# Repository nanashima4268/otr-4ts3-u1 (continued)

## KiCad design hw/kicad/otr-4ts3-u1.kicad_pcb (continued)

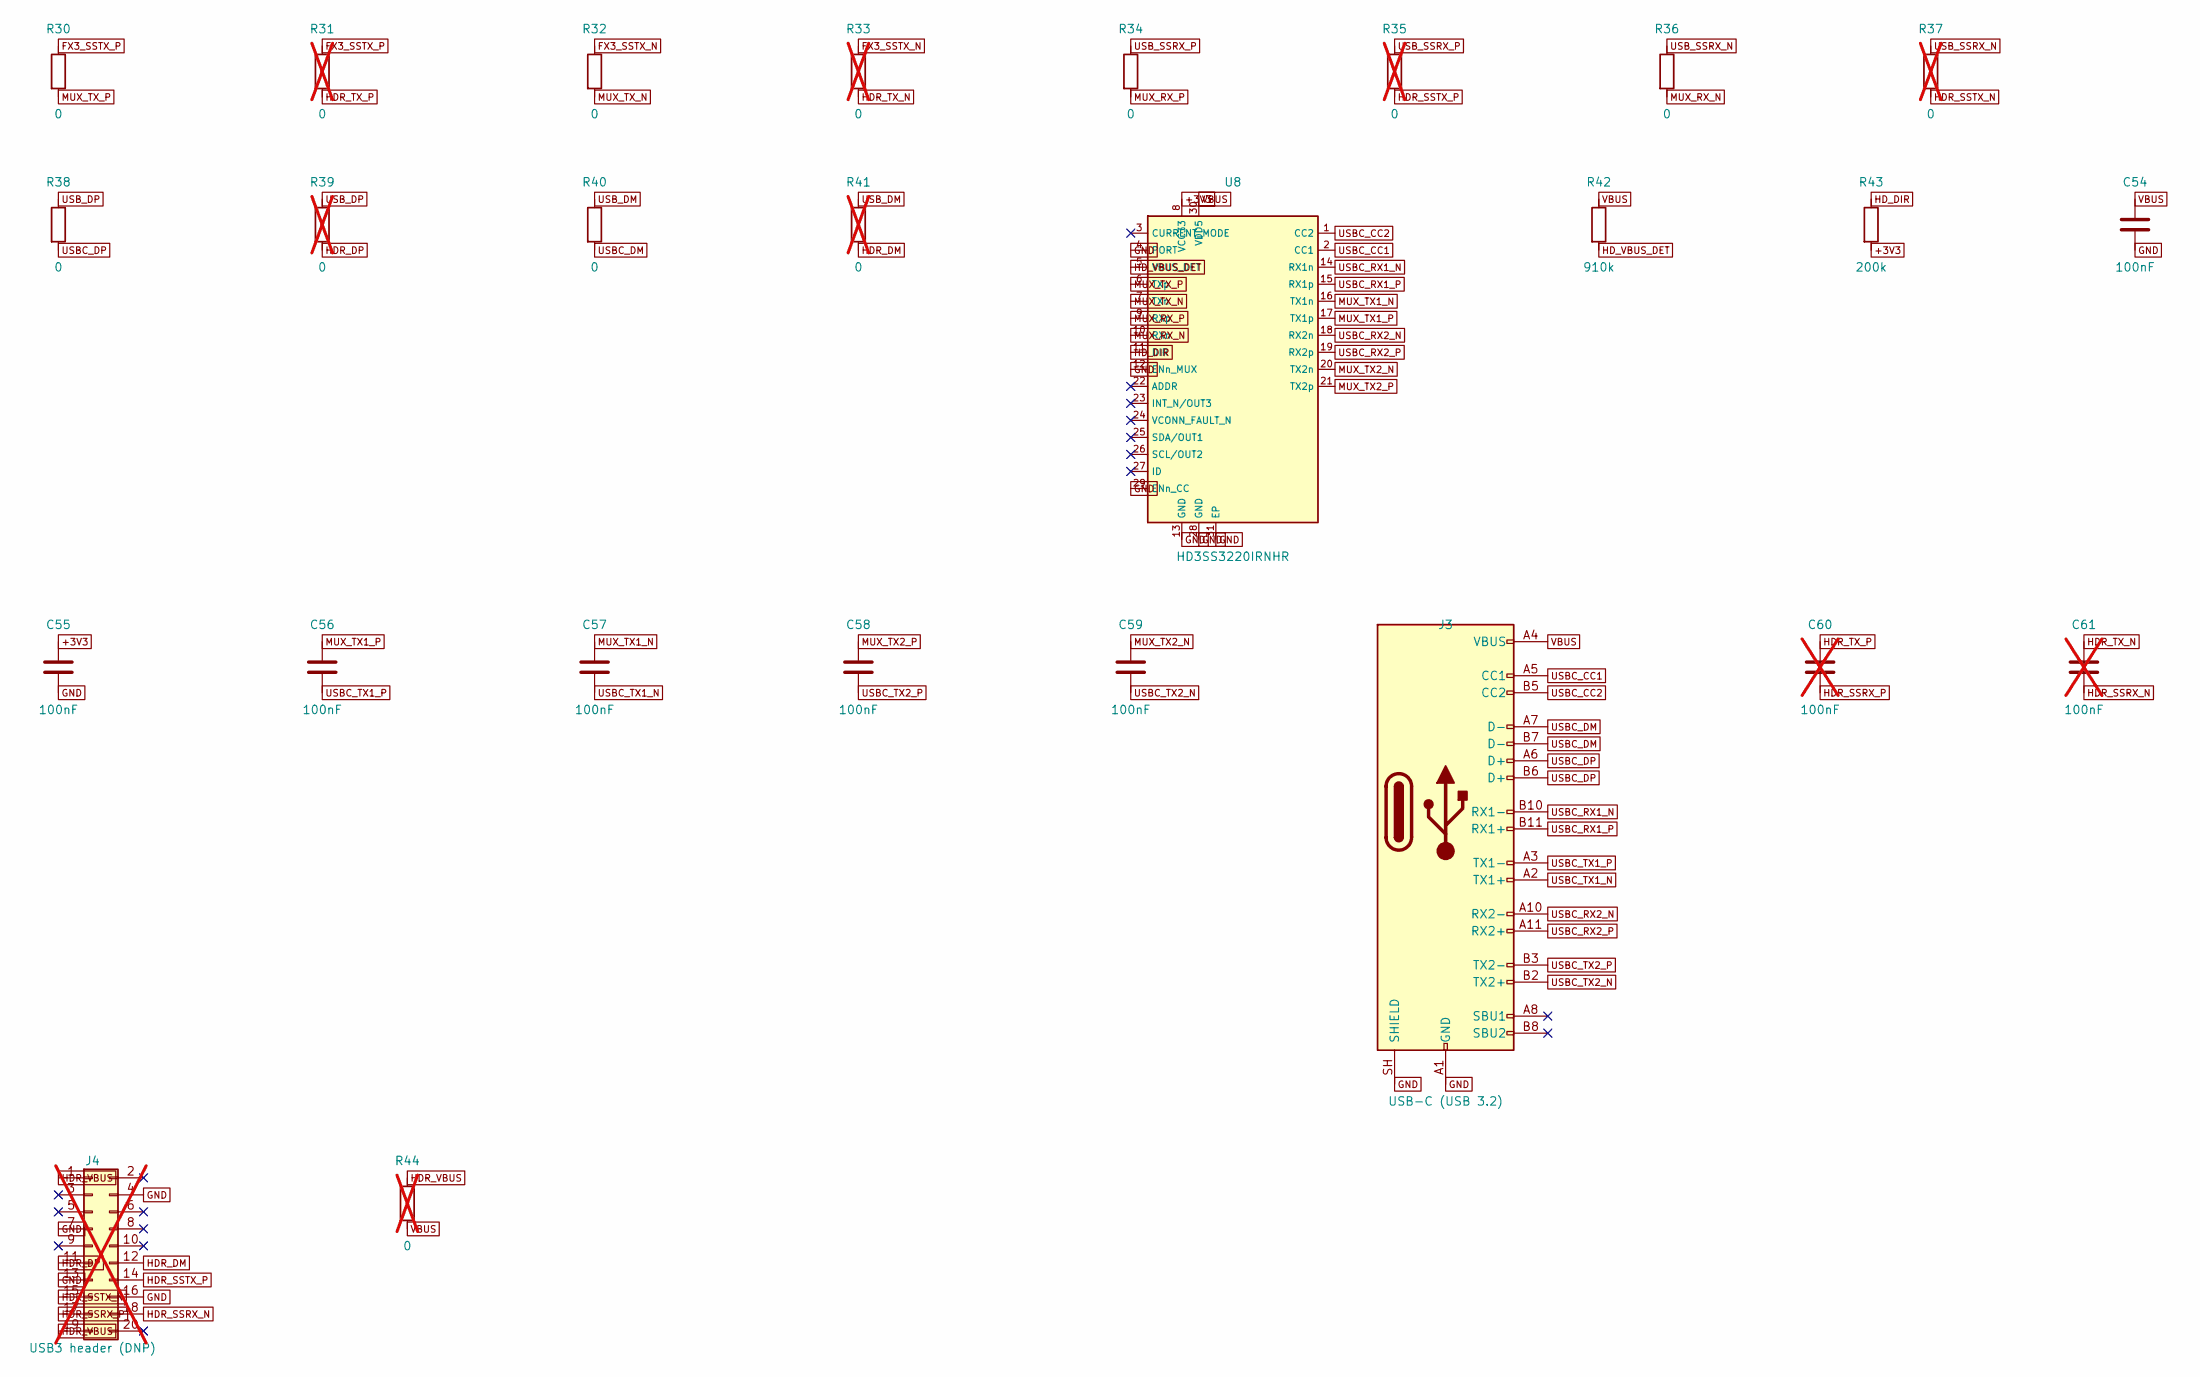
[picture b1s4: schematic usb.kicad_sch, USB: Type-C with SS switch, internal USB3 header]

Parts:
C54, C55, C56, C57, C58, C59: 100nF; C_0402_1005Metric; LCSC C1525
C60, C61: 100nF; C_0402_1005Metric; LCSC C1525; not fitted
J3: USB-C (USB 3.2); USB_C_Receptacle_SameSky_UJ32-C-H-G-H2-SMT; LCSC C22359755
J4: USB3 header (DNP); PinHeader_2x10_P2.00mm_Vertical; not fitted
R30, R32, R34, R36, R38, R40: 0; R_0402_1005Metric; LCSC C17168
R31, R33, R35, R37, R39, R41, R44: 0; R_0402_1005Metric; LCSC C17168; not fitted
R42: 910k; R_0402_1005Metric; LCSC C2909391
R43: 200k; R_0402_1005Metric; LCSC C25764
U8: HD3SS3220IRNHR; Texas_RNH0030A_WQFN-30-1EP_2.5x4.5mm_P0.4mm_EP1.2x3.2mm; LCSC C701817

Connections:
+3V3: C55.1, R43.2, U8.8 (VCC33); also elsewhere on the board
FX3_SSTX_N: R32.1, R33.1; also elsewhere on the board
FX3_SSTX_P: R30.1, R31.1; also elsewhere on the board
GND: C54.2, C55.2, J3.A1 (GND), J3.A12 (GND), J3.B1 (GND), J3.B12 (GND), J3.SH (SHIELD), J4.4, J4.7, J4.13, J4.16, U8.4 (PORT), U8.12 (ENn_MUX), U8.13 (GND), U8.28 (GND), U8.29 (ENn_CC), U8.31 (EP); also elsewhere on the board
HDR_DM: J4.12, R41.2
HDR_DP: J4.11, R39.2
HDR_SSRX_N: C61.2, J4.18
HDR_SSRX_P: C60.2, J4.17
HDR_SSTX_N: J4.15, R37.2
HDR_SSTX_P: J4.14, R35.2
HDR_TX_N: C61.1, R33.2
HDR_TX_P: C60.1, R31.2
HDR_VBUS: J4.1, J4.19, R44.1
HD_DIR: R43.1, U8.11 (DIR)
HD_VBUS_DET: R42.2, U8.5 (VBUS_DET)
MUX_RX_N: R36.2, U8.10 (RXn)
MUX_RX_P: R34.2, U8.9 (RXp)
MUX_TX1_N: C57.1, U8.16 (TX1n)
MUX_TX1_P: C56.1, U8.17 (TX1p)
MUX_TX2_N: C59.1, U8.20 (TX2n)
MUX_TX2_P: C58.1, U8.21 (TX2p)
MUX_TX_N: R32.2, U8.7 (TXn)
MUX_TX_P: R30.2, U8.6 (TXp)
USBC_CC1: J3.A5 (CC1), U8.2 (CC1)
USBC_CC2: J3.B5 (CC2), U8.1 (CC2)
USBC_DM: J3.A7 (D-), J3.B7 (D-), R40.2
USBC_DP: J3.A6 (D+), J3.B6 (D+), R38.2
USBC_RX1_N: J3.B10 (RX1-), U8.14 (RX1n)
USBC_RX1_P: J3.B11 (RX1+), U8.15 (RX1p)
USBC_RX2_N: J3.A10 (RX2-), U8.18 (RX2n)
USBC_RX2_P: J3.A11 (RX2+), U8.19 (RX2p)
USBC_TX1_N: C57.2, J3.A2 (TX1+)
USBC_TX1_P: C56.2, J3.A3 (TX1-)
USBC_TX2_N: C59.2, J3.B2 (TX2+)
USBC_TX2_P: C58.2, J3.B3 (TX2-)
USB_DM: R40.1, R41.1; also elsewhere on the board
USB_DP: R38.1, R39.1; also elsewhere on the board
USB_SSRX_N: R36.1, R37.1; also elsewhere on the board
USB_SSRX_P: R34.1, R35.1; also elsewhere on the board
VBUS: C54.1, J3.A4 (VBUS), J3.A9 (VBUS), J3.B4 (VBUS), J3.B9 (VBUS), R42.1, R44.2, U8.30 (VDD5); also elsewhere on the board

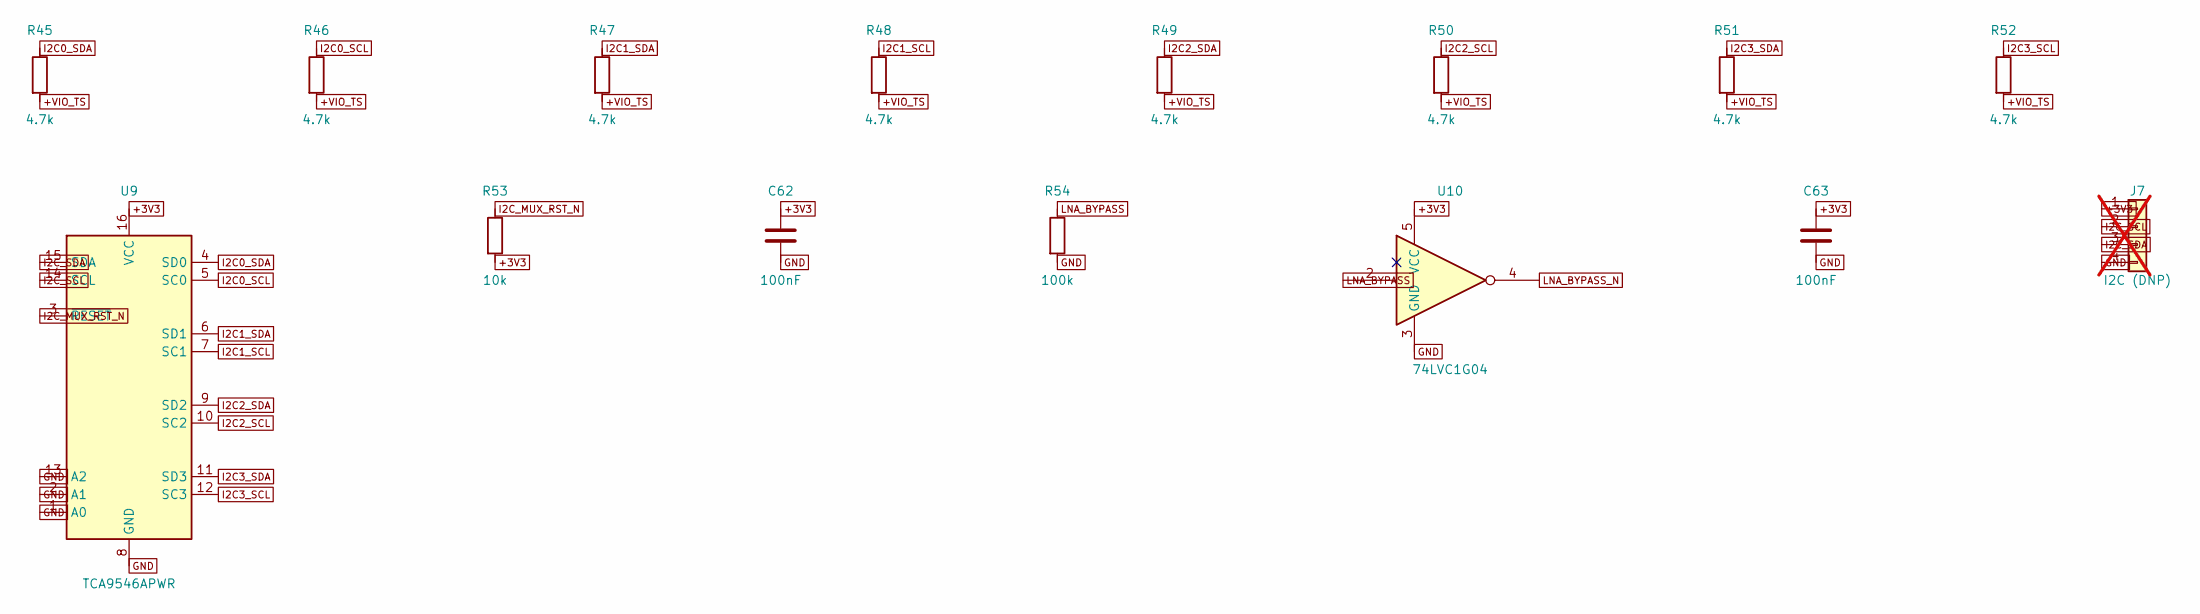
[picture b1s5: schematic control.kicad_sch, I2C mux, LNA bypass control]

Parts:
C62, C63: 100nF; C_0402_1005Metric; LCSC C1525
J7: I2C (DNP); PinHeader_1x04_P2.54mm_Vertical; not fitted
R45, R46, R47, R48, R49, R50, R51, R52: 4.7k; R_0402_1005Metric; LCSC C25900
R53: 10k; R_0402_1005Metric; LCSC C25744
R54: 100k; R_0402_1005Metric; LCSC C25741
U9: TCA9546APWR; TSSOP-16_4.4x5mm_P0.65mm; LCSC C201653
U10: 74LVC1G04; SOT-353_SC-70-5; LCSC C264081

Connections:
+3V3: C62.1, C63.1, J7.1, R53.2, U9.16 (VCC), U10.5 (VCC); also elsewhere on the board
+VIO_TS: R45.2, R46.2, R47.2, R48.2, R49.2, R50.2, R51.2, R52.2; also elsewhere on the board
GND: C62.2, C63.2, J7.4, R54.2, U9.1 (A0), U9.2 (A1), U9.8 (GND), U9.13 (A2), U10.3 (GND); also elsewhere on the board
I2C0_SCL: R46.1, U9.5 (SC0)
I2C0_SDA: R45.1, U9.4 (SD0)
I2C1_SCL: R48.1, U9.7 (SC1)
I2C1_SDA: R47.1, U9.6 (SD1)
I2C2_SCL: R50.1, U9.10 (SC2)
I2C2_SDA: R49.1, U9.9 (SD2)
I2C3_SCL: R52.1, U9.12 (SC3)
I2C3_SDA: R51.1, U9.11 (SD3)
I2C_MUX_RST_N: R53.1, U9.3 (~RESET)
I2C_SCL: J7.2, U9.14 (SCL); also elsewhere on the board
I2C_SDA: J7.3, U9.15 (SDA); also elsewhere on the board
LNA_BYPASS: R54.1, U10.2; also elsewhere on the board
LNA_BYPASS_N: U10.4; also elsewhere on the board

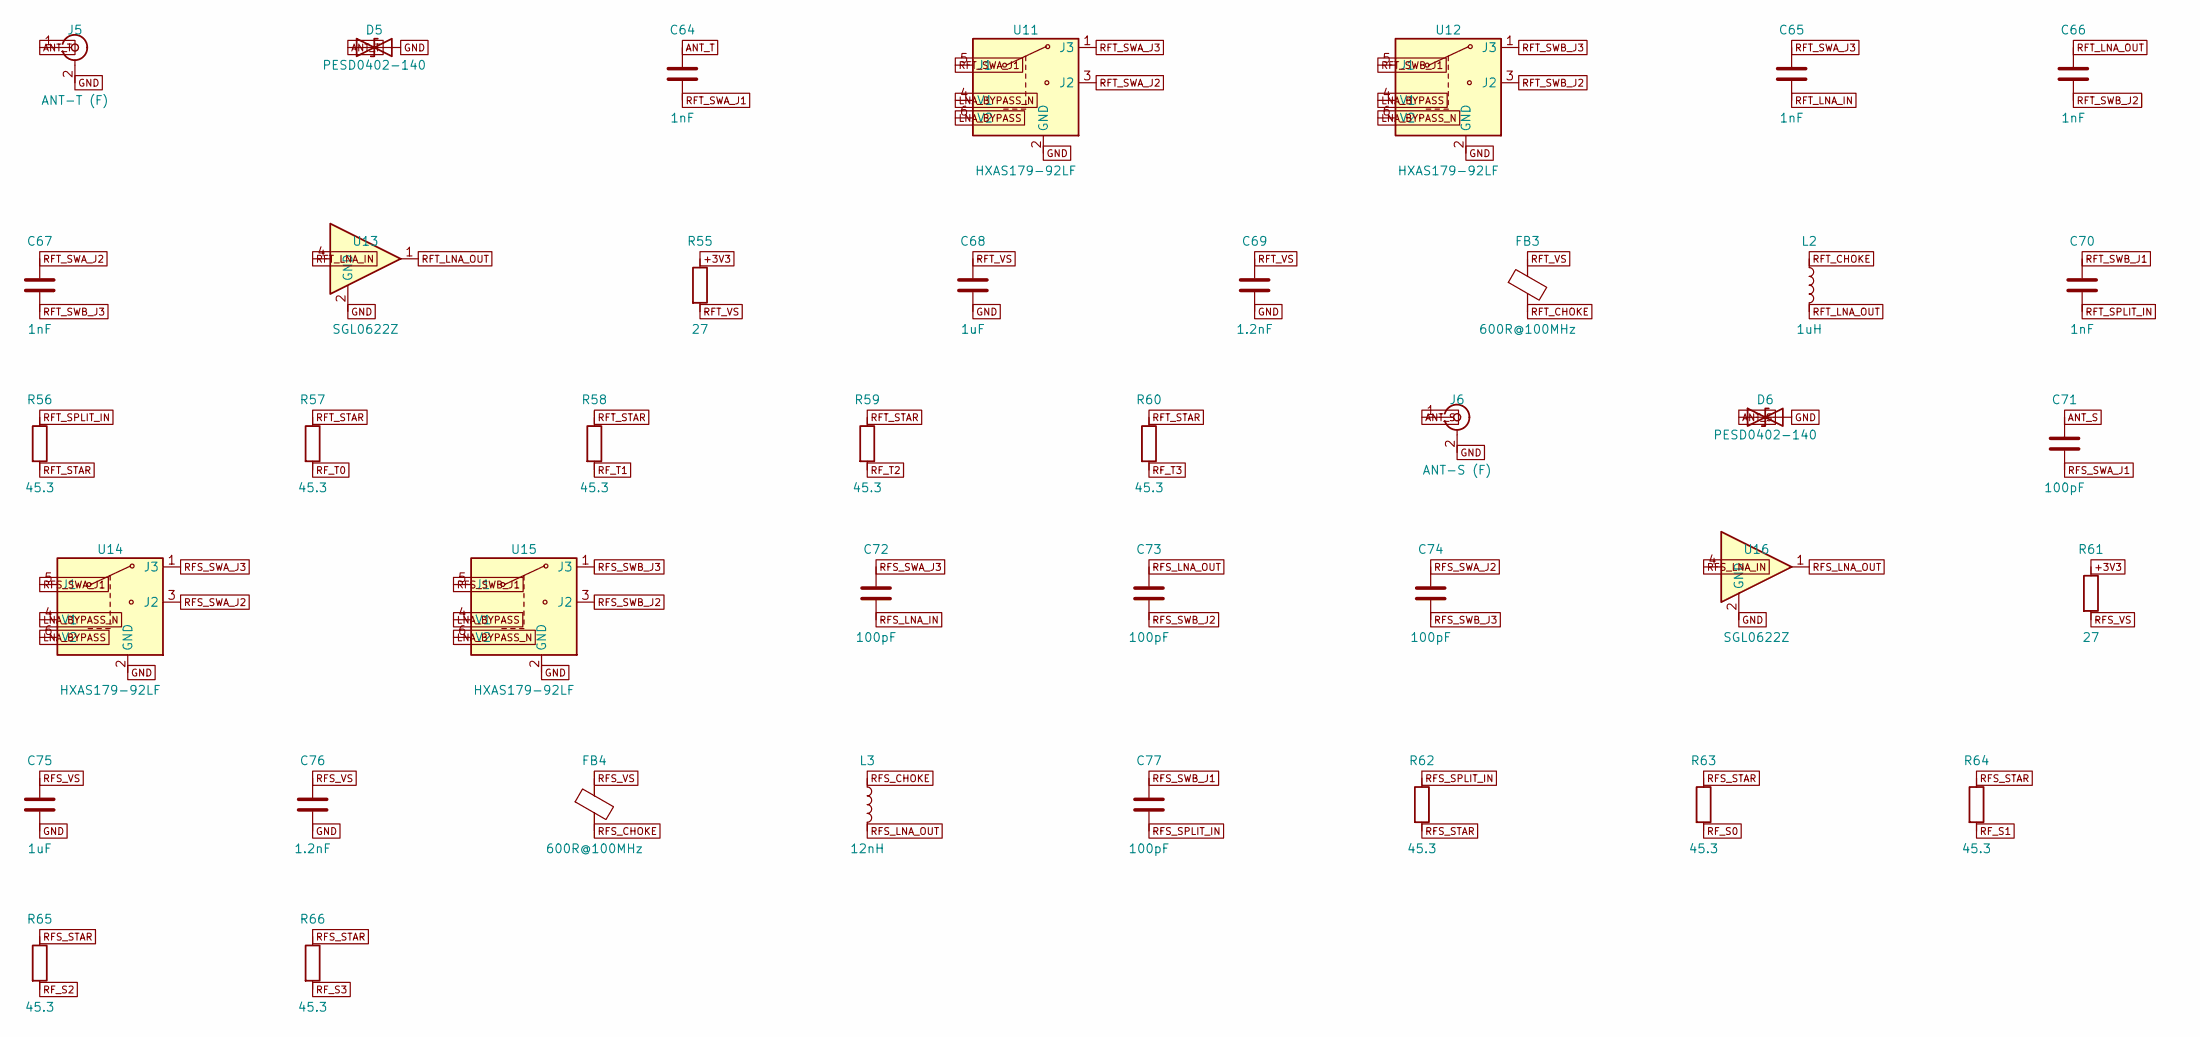
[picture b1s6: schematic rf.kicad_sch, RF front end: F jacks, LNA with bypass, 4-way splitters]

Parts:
C64, C65, C66, C67, C70: 1nF; C_0402_1005Metric; LCSC C1523
C68, C75: 1uF; C_0402_1005Metric; LCSC C52923
C69, C76: 1.2nF; C_0402_1005Metric; LCSC C3010430
C71, C72, C73, C74, C77: 100pF; C_0402_1005Metric; LCSC C1546
D5, D6: PESD0402-140; D_0402_1005Metric; LCSC C10662
FB3, FB4: 600R@100MHz; L_0402_1005Metric; LCSC C76890
J5: ANT-T (F); F_Female_DOSIN_DS803FPR0016_Horizontal; LCSC C2979612
J6: ANT-S (F); F_Female_DOSIN_DS803FPR0016_Horizontal; LCSC C2979612
L2: 1uH; L_0603_1608Metric; LCSC C98326
L3: 12nH; L_0402_1005Metric; LCSC C77104
R55, R61: 27; R_0402_1005Metric; LCSC C25156
R56, R57, R58, R59, R60, R62, R63, R64, R65, R66: 45.3; R_0402_1005Metric; LCSC C5126226
U11, U12, U14, U15: HXAS179-92LF; SOT-363_SC-70-6; LCSC C49010110
U13, U16: SGL0622Z; DFN-8-1EP_2x2mm_P0.5mm_EP0.9x1.6mm; LCSC C470895

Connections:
+3V3: R55.1, R61.1; also elsewhere on the board
ANT_S: C71.1, D6.1 (A1), J6.1 (In)
ANT_T: C64.1, D5.1 (A1), J5.1 (In)
GND: C68.2, C69.2, C75.2, C76.2, D5.2 (A2), D6.2 (A2), J5.2 (Ext), J6.2 (Ext), U11.2 (GND), U12.2 (GND), U13.2 (GND), U13.3 (GND), U13.5 (GND), U13.6 (GND), U13.7 (GND), U13.8 (GND), U13.9 (GND), U14.2 (GND), U15.2 (GND), U16.2 (GND), U16.3 (GND), U16.5 (GND), U16.6 (GND), U16.7 (GND), U16.8 (GND), U16.9 (GND); also elsewhere on the board
LNA_BYPASS: U11.6 (V2), U12.4 (V1), U14.6 (V2), U15.4 (V1); also elsewhere on the board
LNA_BYPASS_N: U11.4 (V1), U12.6 (V2), U14.4 (V1), U15.6 (V2); also elsewhere on the board
RFS_CHOKE: FB4.2, L3.1
RFS_LNA_IN: C72.2, U16.4
RFS_LNA_OUT: C73.1, L3.2, U16.1
RFS_SPLIT_IN: C77.2, R62.1
RFS_STAR: R62.2, R63.1, R64.1, R65.1, R66.1
RFS_SWA_J1: C71.2, U14.5 (J1)
RFS_SWA_J2: C74.1, U14.3 (J2)
RFS_SWA_J3: C72.1, U14.1 (J3)
RFS_SWB_J1: C77.1, U15.5 (J1)
RFS_SWB_J2: C73.2, U15.3 (J2)
RFS_SWB_J3: C74.2, U15.1 (J3)
RFS_VS: C75.1, C76.1, FB4.1, R61.2
RFT_CHOKE: FB3.2, L2.1
RFT_LNA_IN: C65.2, U13.4
RFT_LNA_OUT: C66.1, L2.2, U13.1
RFT_SPLIT_IN: C70.2, R56.1
RFT_STAR: R56.2, R57.1, R58.1, R59.1, R60.1
RFT_SWA_J1: C64.2, U11.5 (J1)
RFT_SWA_J2: C67.1, U11.3 (J2)
RFT_SWA_J3: C65.1, U11.1 (J3)
RFT_SWB_J1: C70.1, U12.5 (J1)
RFT_SWB_J2: C66.2, U12.3 (J2)
RFT_SWB_J3: C67.2, U12.1 (J3)
RFT_VS: C68.1, C69.1, FB3.1, R55.2
RF_S0: R63.2
RF_S1: R64.2
RF_S2: R65.2
RF_S3: R66.2
RF_T0: R57.2
RF_T1: R58.2
RF_T2: R59.2
RF_T3: R60.2

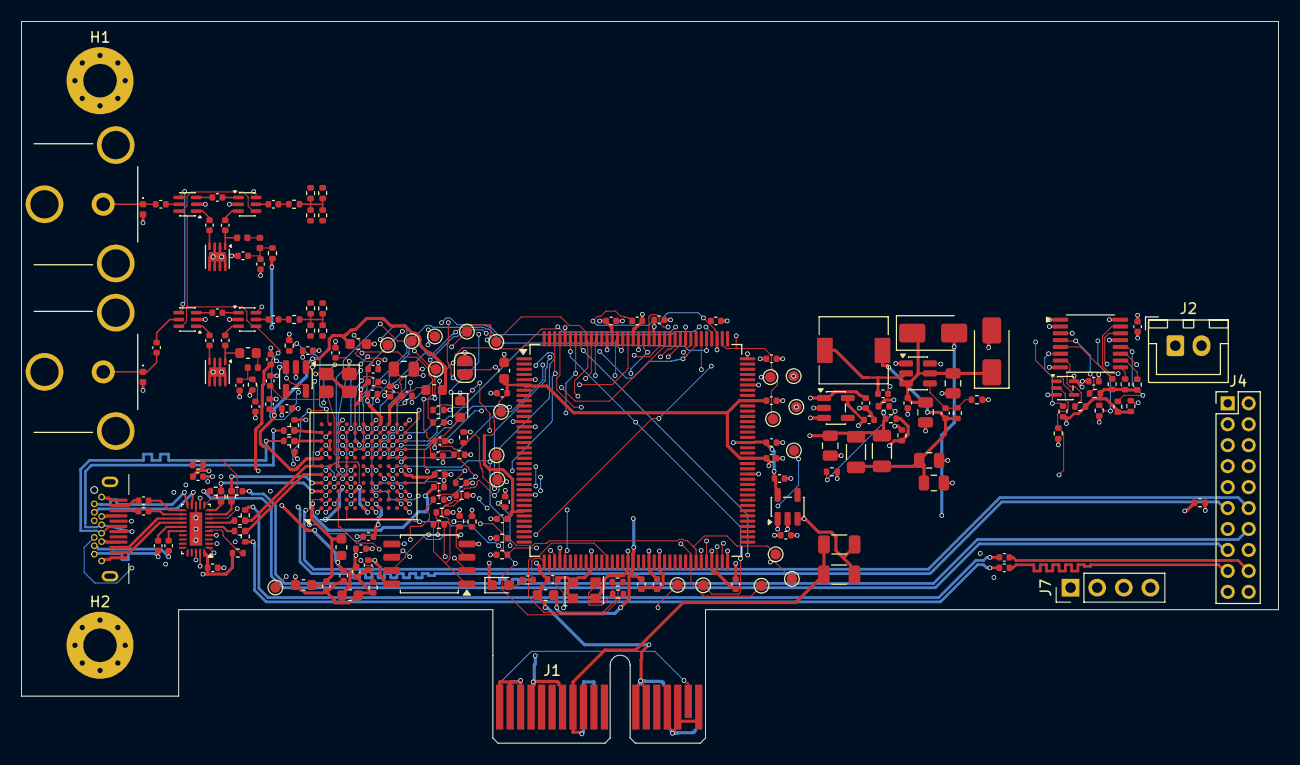
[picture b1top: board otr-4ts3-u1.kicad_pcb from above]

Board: 6 copper layers, 120.0 x 68.9 mm, 204 parts (0 on the bottom side), 154 nets.

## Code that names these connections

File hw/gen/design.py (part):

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    gpio = {i: "NC" for i in range(60)}
    for i in range(16):
        gpio[i] = f"GPIF_DQ{i}"
    gpio.update({16: "GPIF_PCLK", 17: "GPIF_SLCS_N", 18: "GPIF_SLWR_N", 19: "GPIF_SLOE_N",
                 20: "GPIF_SLRD_N", 21: "GPIF_FLAGA", 22: "GPIF_FLAGB", 24: "GPIF_PKTEND_N",
                 28: "GPIF_A1", 29: "GPIF_A0",
                 30: "FX3_PMODE0", 31: "NC", 32: "FX3_PMODE2",
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    decouple(s, "+3V3", n100=1)
    s.add(R("33", "CLK50", "FPGA_CLK50"), R("33", "CLK50", "GPIF_PCLK"))
    # status LED and test pads on gpio_out (FPGA register 0x08)
    s.add(R("1k", "FPGA_GPIO0", "FPGA_LED_A"))
    s.add(Part(ref("D"), "Device:LED", "LED", "LED_SMD:LED_0603_1608Metric",
               {"1": "GND", "2": "FPGA_LED_A"}, lcsc="C2286"))
    for i in (1, 2, 3):
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    s.add(Part(ref("U"), "Interface_Expansion:TCA9546APW", "TCA9546APWR", "Package_SO:TSSOP-16_4.4x5mm_P0.65mm",
               mux, lcsc="C201653"))
    s.add(R("10k", "I2C_MUX_RST_N", "+3V3"), C("100n", "+3V3"))
    # LNA_BYPASS (FX3 GPIO43): 0 = LNA in path (pulled down while the FX3 boots)
    s.add(R("100k", "LNA_BYPASS", "GND"))
    s.add(Part(ref("U"), "74xGxx:74LVC1G04", "74LVC1G04", "Package_TO_SOT_SMD:SOT-353_SC-70-5",
               {"1": "NC", "2": "LNA_BYPASS", "3": "GND", "4": "LNA_BYPASS_N", "5": "+3V3"}, lcsc="C264081"))
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    - an I2C header on the FX3 side of the TCA9546A (DNP), for reading the
      demodulator chip IDs with an external adapter (D-21)"""
    fpga = next(sh for sh in d.sheets if sh.name == "fpga")
    for net, label in (("GPIF_PCLK", "PCLK"), ("GPIF_SLCS_N", "SLCS#"), ("GPIF_SLWR_N", "SLWR#"),
                       ("GPIF_FLAGA", "FLAGA"), ("GPIF_FLAGB", "FLAGB"), ("GPIF_DQ0", "DQ0"),
                       ("FPGA_CDONE", "CDONE"), ("FPGA_CRESET_B", "CRESET_B"),
                       ("GND", "GND"), ("GND", "GND")):
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
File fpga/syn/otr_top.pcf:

# Generated by hw/gen/design.py from the schematic pin plan; do not edit.
# iCE40HX4K-TQ144 (nextpnr: --hx8k --package tq144:4k).
set_io dq[0] 110
set_io dq[5] 112
set_io dq[1] 113
set_io dq[4] 114
set_io dq[3] 115
set_io dq[7] 116
set_io dq[6] 117
set_io dq[8] 118
set_io pktend_n 119
set_io dq[10] 120
set_io dq[12] 121
set_io dq[13] 122
set_io dq[11] 124
set_io dq[9] 125
set_io dq[15] 128
set_io dq[14] 129
set_io slcs_n 130
set_io slrd_n 134
set_io sloe_n 135
set_io slwr_n 136
set_io flaga 137
set_io dq[2] 138
set_io flagb 139
set_io fifo_addr[0] 141
set_io fifo_addr[1] 142
set_io ts_clk[0] 20
set_io ts_data[0] 19
set_io ts_valid[0] 18
set_io ts_sync[0] 17
set_io ts_clk[1] 21
set_io ts_data[1] 22
set_io ts_valid[1] 23
set_io ts_sync[1] 24
set_io ts_clk[2] 93
set_io ts_data[2] 91
set_io ts_valid[2] 90
set_io ts_sync[2] 88
set_io ts_clk[3] 94
set_io ts_data[3] 95
set_io ts_valid[3] 96
set_io ts_sync[3] 97
set_io clk 49
set_io gpio_out[0] 37
set_io gpio_out[1] 38
set_io gpio_out[2] 39
set_io gpio_out[3] 41
set_io spi_miso 67
set_io spi_mosi 68
set_io spi_sck 70
set_io spi_ss_n 71
